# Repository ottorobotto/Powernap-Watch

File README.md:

# PowerNap PCB, spin 1

First circuit board for the PowerNap watch: 32 x 40 mm, 4 layers, 66 parts placed by the factory.
Design notes and the reasons behind every choice: `docs/pcb-spin1-design.md`. The case: `case/README.md`.

**Read section 5 ("What has and has not been checked") before paying for anything.**

## 1. What is in this folder

| Path | What |
|---|---|
| `PowerNap_spin1.kicad_pro` | Open this in KiCad 10 to look at the schematic and the board. |
| `fab/PowerNap_spin1_gerbers.zip` | The board itself, for JLCPCB ("Gerber file"). |
| `fab/PowerNap_spin1_bom.csv` | The parts list with JLCPCB part numbers ("BOM file"). |
| `fab/PowerNap_spin1_cpl.csv` | Where each part goes and how it is turned ("CPL file"). |
| `fab/PowerNap_spin1_board.step` | 3D model of the board. |
| `out/PowerNap_spin1_schematic.pdf` | The schematic as a PDF. |
| `out/board_report.txt`, `out/stock.txt` | The last automatic board check and the last stock check. |
| `out/final_top.png`, `final_bottom.png`, `final_in1_ground.png`, `final_in2_3v3.png` | Pictures of the four copper layers. |
| `scripts/` | The programs that generate all of the above from one description (`design.py`). |
| `case/` | The 3D-printed case. |

Nothing here was drawn by hand. `scripts/design.py` lists every part and what each pin connects to;
`scripts/placement.py` says where each part sits. To change the design, change those and rebuild (section 6).

## 2. What the board does differently from the Arduino prototype

- It uses the same processor (nRF52840, inside the u-blox BMD-340 module) on the **same pins** as the
  Arduino Nano 33 BLE. So it runs the same firmware and is programmed from the Arduino IDE as a "Nano 33 BLE".
- Pulse sensor (MAX30101) on the **underside**, alone, so it can touch the skin through the case.
- Accelerometer BMI270 (the one all naps were recorded with). No magnetometer, no temperature sensor.
- USB-C for charging, uploading and the serial log. LiPo charger (100 mA) on board.
- On/off slide switch. Charging works in both positions.
- Buzzer (4 kHz) instead of the breadboard beeper; user button on the side; reset button behind a pin-hole.
- Status lights like the Arduino's: red/green/blue, the yellow "L" light, plus a red charging light.
- Five holes (`J2`) for the programmer, three test points (1.8 V, LED supply, system voltage).

## 3. Ordering from JLCPCB

Prices change; treat the numbers as rough. The quote on the website is the real one.

1. Go to jlcpcb.com, choose **Instant Quote / Order now**, and upload `fab/PowerNap_spin1_gerbers.zip`.
   It should detect **4 layers, 32 x 40 mm**. If it does not, stop and ask.
2. Board options: quantity **5**; thickness **1.6 mm**; surface finish **ENIG** (flat gold pads — worth the extra
   for the fine-pitch module and sensors); via covering **tented**; everything else as offered.
3. Switch on **PCB Assembly**. Choose **Standard** assembly, **both sides** (the pulse sensor is on the underside),
   quantity 2 or 5. Let JLCPCB add tooling holes and edge rails. Tick **"Confirm parts placement"**.
4. Upload `PowerNap_spin1_bom.csv` and `PowerNap_spin1_cpl.csv`.
5. Parts page: every line should be found and in stock (checked on 15 November 2026, see `out/stock.txt`).
   `J2` and `BT1` are not in the files on purpose — nothing is soldered there by the factory.
   If a part is out of stock, do not accept a suggested replacement without asking.
6. **Placement preview — check these before you pay** (section 5 explains why):
   - `U6` (pulse sensor, underside): its pin-1 dot must match the dot printed on the board.
   - `U1` (the big module): antenna end at the board edge, at the top.
   - `J1` (USB-C): opening pointing out over the right-hand edge.
   - The small chips `U2 U3 U4 U5 U7 U8 Q1 Q2`: pin-1 dot on the board's pin-1 mark.
   - `LED1`–`LED5`, `D1`, `D2`, `LS1` (buzzer, `+` mark).
7. Rough cost for 5 boards, 2 of them assembled: boards about $25 with ENIG, assembly set-up about $50,
   18 "extended" part types x $3 = $54, parts about $24 per board, shipping about $25, then Danish VAT (25 %)
   and a handling fee on top. Expect **roughly 1,500–2,200 DKK** in total. Not a quote.

## 4. First start-up (when the boards arrive)

You need an **nRF52840 DK** (Nordic's development board, about 400 DKK) once, to put the Arduino bootloader
into each new board. A new module is blank and does not show up on USB until this is done.

1. Look before you power: no solder bridges, pulse sensor straight in its place.
2. With a multimeter, check there is **no short** between `3V3` (hole 1 of `J2`, the square one) and `GND` (hole 5).
3. Plug in USB **without a battery**, switch on. Measure: test point `TP3` about 4.6 V; `J2` hole 1 = 3.3 V
   (3.25–3.35). If the 3.3 V is missing or the board gets warm, unplug.
   (The red charge light may glow or flicker with no battery connected. That is normal.)
4. Bootloader: connect the DK's **Debug out** pins to `J2` — hole 1 = 3.3 V (the DK's "VTG"), 2 = SWDIO,
   3 = SWDCLK, 4 = RESET, 5 = GND — and program this file, which is already on your PC:
   `C:\Users\pc\AppData\Local\Arduino15\packages\arduino\hardware\mbed_nano\4.6.0\bootloaders\nano33ble\bootloader.hex`
   with Nordic's "Programmer" app (part of nRF Connect for Desktop). I will walk you through this step when
   you get there.
5. Press reset twice quickly: the yellow light should pulse and a new COM port should appear. From here on
   the board is programmed from the Arduino IDE exactly like the Nano.
6. Firmware: PowerNap v11 with **one line changed**: `IMU.begin()` becomes `IMU.begin(BOSCH_ACCELEROMETER_ONLY)`
   (there is no magnetometer on this board, and the library otherwise waits for one).
   The new buzzer is a different type from the breadboard one, so the quiet "probe" beep (`PROBE_DUTY`)
   needs re-tuning by ear.
7. Only then solder the battery to `BT1` — **measure which wire is + first**. With the battery in, the red
   light is on while charging and goes out when full.

## 5. What has and has not been checked

Checked by program, every time the board is rebuilt:

- The schematic passes KiCad's electrical rule check with 0 messages, and its netlist is identical to `design.py`
  (every net, every pin).
- The board passes KiCad's design rule check with 0 errors (clearances, track widths, shorts, unconnected
  pins, parts overlapping) and matches the schematic part for part and pin for pin. See `out/board_report.txt`.
  What remains are 5 cosmetic notes about silkscreen lines running over the board edge at the USB socket
  and the switches; the factory simply cuts those off.
- No copper in the strip under the antenna. The ground-plane layer carries no tracks at all - it is one
  unbroken sheet (`out/final_in1_ground.png`).
- Every footprint was compared pad by pad with the footprint JLCPCB uses for the same part number, and the
  rotations in the placement file were calculated from that comparison (`scripts/check_rotations.py`).
- The finished placement file was then tested the way the factory uses it: JLCPCB's footprint for each of
  the 66 parts was placed at the file's position and rotation, and its pads compared with the board's.
  All land on their pads; the largest difference is 0.28 mm (`scripts/verify_cpl.py`).
- All 36 part types were in stock at JLCPCB on 15 November 2026.

Checked by me against documents:

- Every pin of every chip against its data sheet or a proven schematic (sources are listed at the top of `design.py`).
- The module's 68-pad footprint against the data sheet drawing and against JLCPCB's own footprint.

**Not checked — the real risks:**

1. **Nobody experienced has looked at this layout.** It was placed by coordinates and routed by programs
   (an automatic router, plus a small one I wrote for the last 22 connections). It obeys the rules, but rules
   do not catch everything (noise near the sensor, radio range, how well it solders). Known blemishes:
   about 37 mm of the 3.3 V and USB supply runs in 0.15 mm tracks instead of the usual 0.25 mm (still several
   times more than the current needs), and one small via sits right against a resistor pad (`R16`). For a first board that is normal, and it is why this is "spin 1" — but if you know
   anyone who designs boards, an hour of their time before ordering is the best money-saver there is.
2. **The underside part's rotation** (`U6`, the pulse sensor) follows the usual convention for bottom-side
   parts (mirrored, angle counted from below), which I could not confirm in JLCPCB's own documentation.
   If it were wrong the sensor would be soldered on turned by half a turn and would not work. That is why
   step 6 of the ordering list matters; JLCPCB's engineers also check pin-1 marks.
3. **The Arduino bootloader on this module** should work (same chip, same pins), but it has not been tried.
4. **The buzzer's loudness** inside the case, and the **radio range** with the battery beside the module,
   are unknown until a board exists.
5. Nothing has been built. A first board commonly needs one or two wire fixes; a second spin is the usual outcome.

## 6. Rebuilding after a change

Run from the project folder, in this order. `KP` means `"C:\Program Files\KiCad\10.0\bin\python.exe"`.

1. `py -3.11 hardware/spin1/scripts/gen_schematic.py` — writes the schematic
2. `py -3.11 hardware/spin1/scripts/verify_schematic.py` — must end with `SCHEMATIC OK`
3. `KP hardware/spin1/scripts/gen_board.py` — places the parts
4. `KP hardware/spin1/scripts/route_board.py` — routes (about 10 minutes). The automatic router does not give
   the same result twice; add `--reuse` to keep its last result and only redo the steps after it.
5. `KP hardware/spin1/scripts/verify_board.py` — must end with `BOARD OK`
6. `KP hardware/spin1/scripts/check_rotations.py` — only if a part or footprint changed
7. `py -3.11 hardware/spin1/scripts/export_fab.py` — writes `fab/`
8. `KP hardware/spin1/scripts/verify_cpl.py` — must end with `PLACEMENT FILE OK`
9. `py -3.11 hardware/spin1/scripts/check_stock.py` — live stock
10. `KP hardware/spin1/scripts/dump_bodies.py`, then Blender with `case/build_case.py` — rebuilds the case

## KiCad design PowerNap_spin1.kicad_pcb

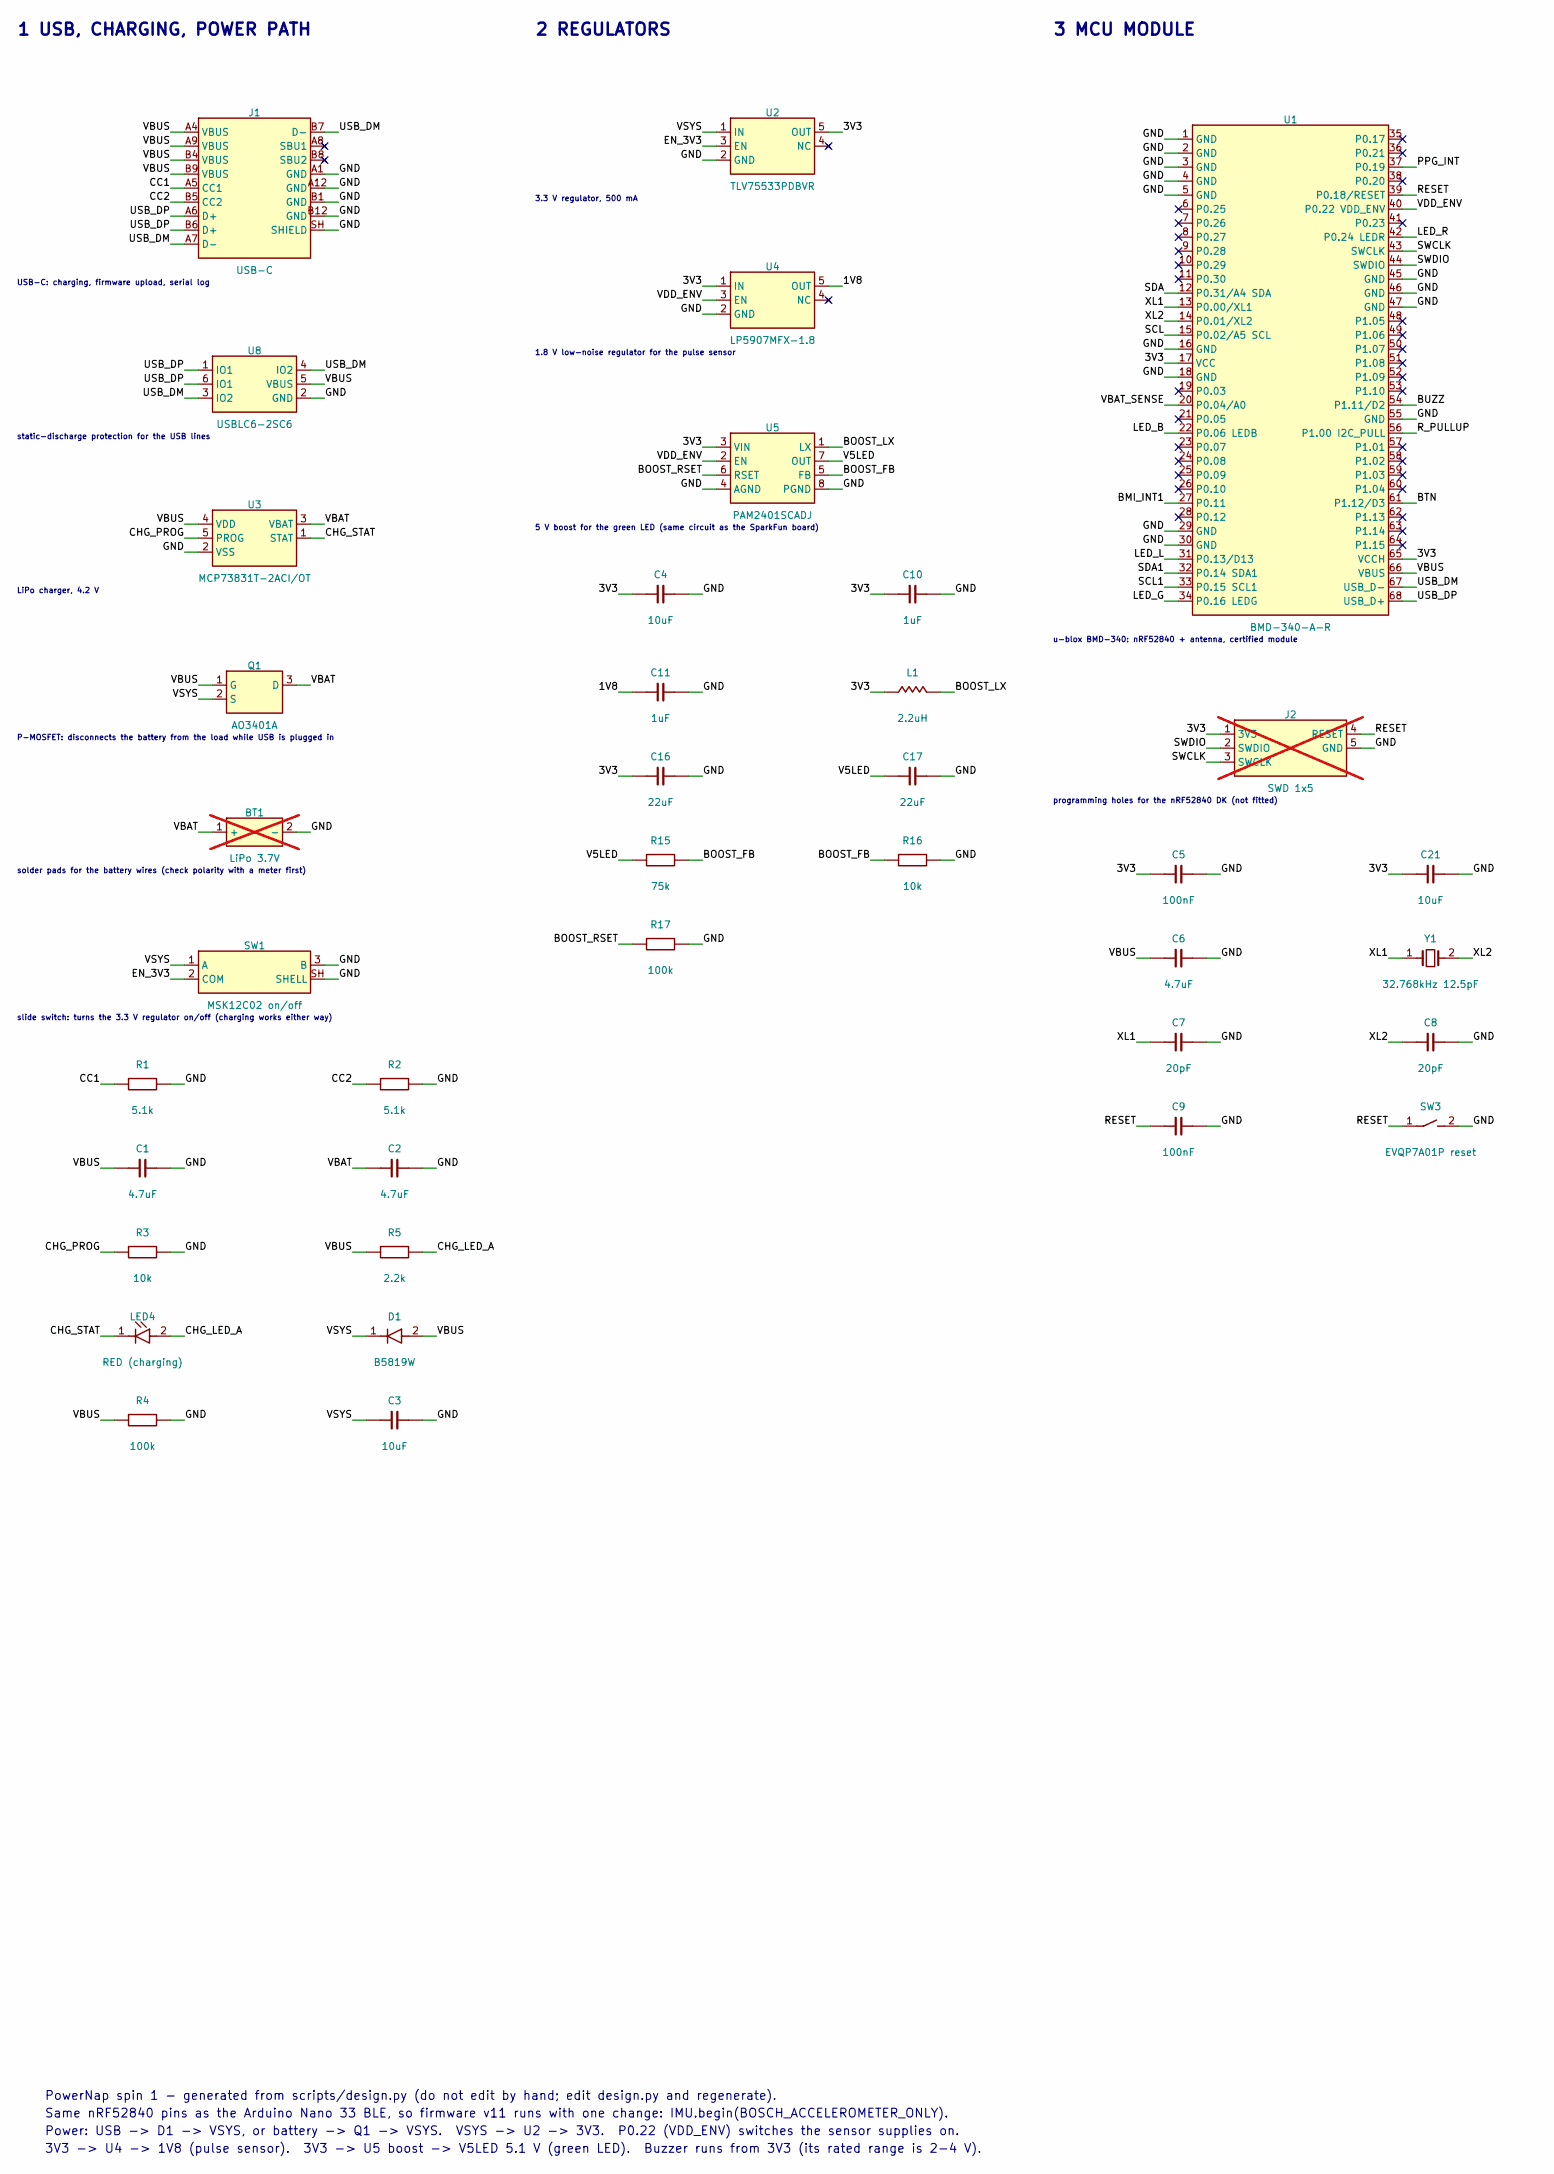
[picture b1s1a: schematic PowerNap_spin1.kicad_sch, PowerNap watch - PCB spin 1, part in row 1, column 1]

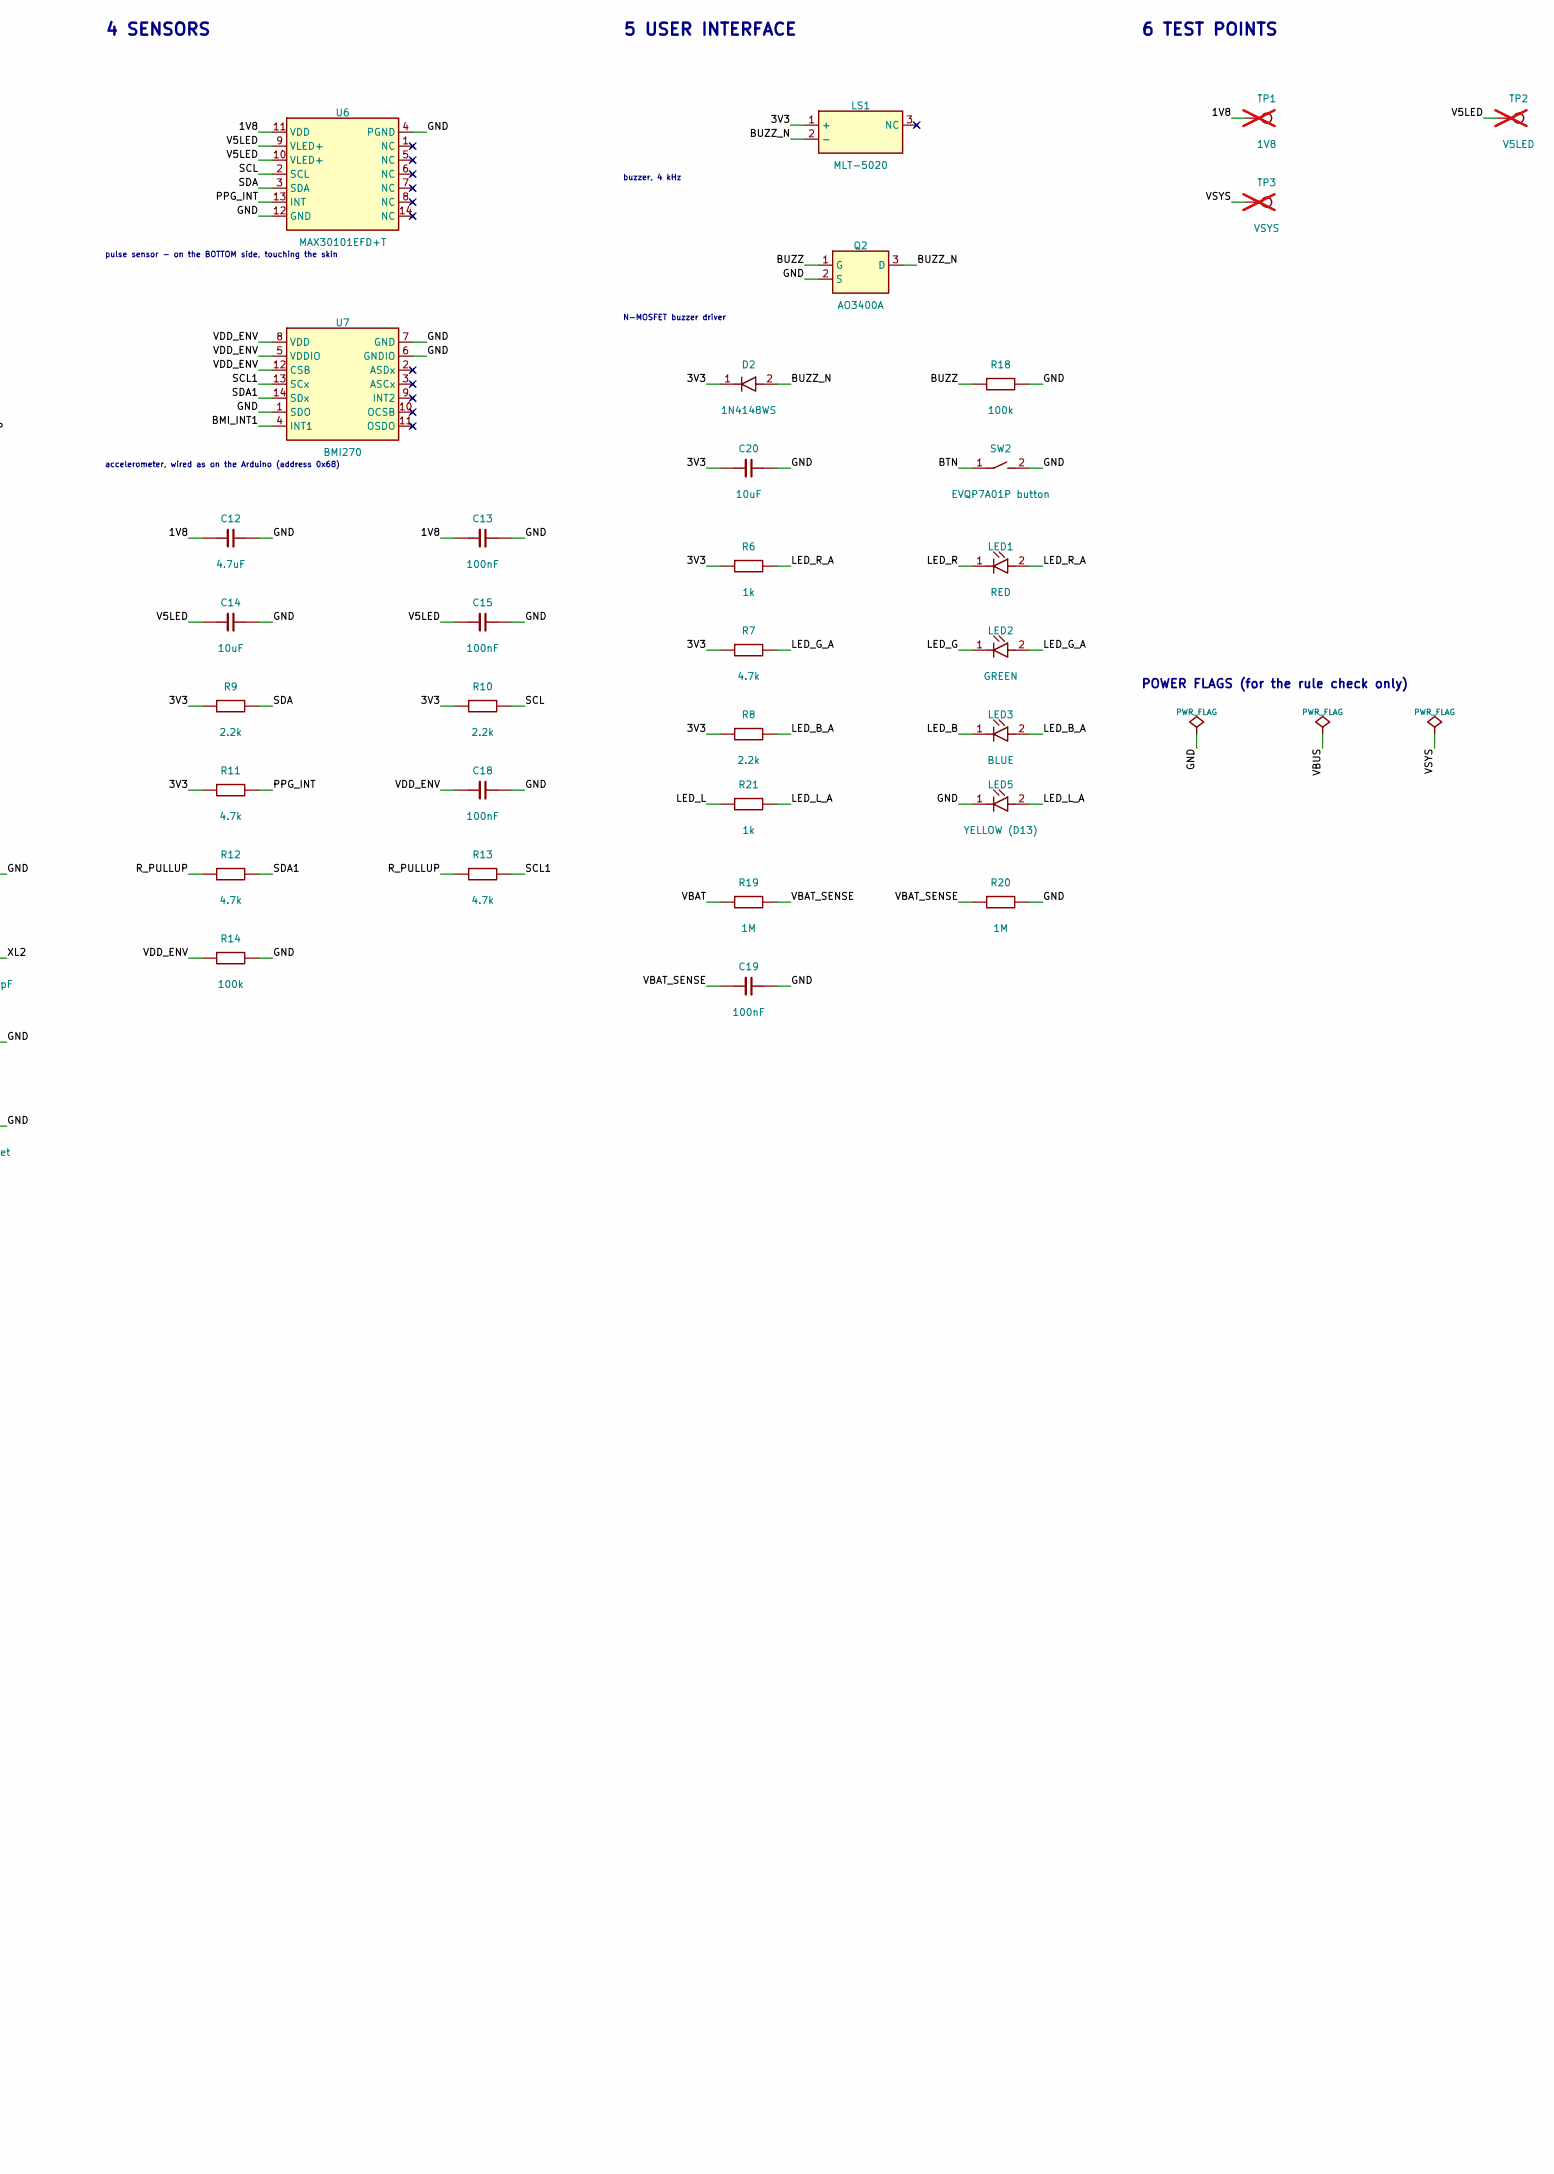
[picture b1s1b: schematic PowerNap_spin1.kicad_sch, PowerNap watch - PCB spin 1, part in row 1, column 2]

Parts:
BT1: LiPo 3.7V; BatteryPads; MPN LiPo 3.7V; not fitted
C1, C2, C6, C12: 4.7uF; C_0402_1005Metric; MPN SMD:C 4.7uF; LCSC C23733
C3, C4, C14, C20, C21: 10uF; C_0603_1608Metric; MPN SMD:C 10uF; LCSC C19702
C5, C9, C13, C15, C18, C19: 100nF; C_0402_1005Metric; MPN SMD:C 100nF; LCSC C1525
C7, C8: 20pF; C_0402_1005Metric; MPN SMD:C 20pF; LCSC C1554
C10, C11: 1uF; C_0402_1005Metric; MPN SMD:C 1uF; LCSC C52923
C16, C17: 22uF; C_0603_1608Metric; MPN SMD:C 22uF; LCSC C59461
D1: B5819W; D_SOD-123; MPN B5819W; LCSC C8598
D2: 1N4148WS; D_SOD-323; MPN 1N4148WS; LCSC C2128
J1: USB-C; USB_C_Receptacle_HRO_TYPE-C-31-M-12; MPN HRO TYPE-C-31-M-12; LCSC C165948
J2: SWD 1x5; PinHeader_1x05_P2.54mm_Vertical; MPN SWD 1x5; not fitted
L1: 2.2uH; L_Sunlord_SWPA3015S; MPN SWPA3015S2R2MT; LCSC C43389
LED1: RED; LED_0603_1608Metric; MPN KT-0603R; LCSC C2286
LED2: GREEN; LED_0603_1608Metric; MPN XL-1608UGC-04; LCSC C965804
LED3: BLUE; LED_0603_1608Metric; MPN XL-1608UBC-04; LCSC C965807
LED4: RED (charging); LED_0603_1608Metric; MPN KT-0603R; LCSC C2286
LED5: YELLOW (D13); LED_0603_1608Metric; MPN XL-1608UYC-06; LCSC C965802
LS1: MLT-5020; MPN MLT-5020; LCSC C94598
Q1: AO3401A; SOT-23; MPN AO3401A; LCSC C15127
Q2: AO3400A; SOT-23; MPN AO3400A; LCSC C20917
R1, R2: 5.1k; R_0402_1005Metric; MPN 0402 5.1k 1%; LCSC C25905
R3, R16: 10k; R_0402_1005Metric; MPN 0402 10k 1%; LCSC C25744
R4, R14, R17, R18: 100k; R_0402_1005Metric; MPN 0402 100k 1%; LCSC C25741
R5, R8, R9, R10: 2.2k; R_0402_1005Metric; MPN 0402 2.2k 1%; LCSC C25879
R6, R21: 1k; R_0402_1005Metric; MPN 0402 1k 1%; LCSC C11702
R7, R11, R12, R13: 4.7k; R_0402_1005Metric; MPN 0402 4.7k 1%; LCSC C25900
R15: 75k; R_0402_1005Metric; MPN 0402 75k 1%; LCSC C25798
R19, R20: 1M; R_0402_1005Metric; MPN 0402 1M 1%; LCSC C26083
SW1: MSK12C02 on/off; SW_SPDT_Shouhan_MSK12C02; MPN MSK12C02; LCSC C431540
SW2: EVQP7A01P button; SW_SPST_EVQP7A; MPN EVQP7A01P; LCSC C79167
SW3: EVQP7A01P reset; SW_SPST_EVQP7A; MPN EVQP7A01P; LCSC C79167
TP1: 1V8; TestPoint_Pad_D1.0mm; MPN 1V8; not fitted
TP2: V5LED; TestPoint_Pad_D1.0mm; MPN V5LED; not fitted
TP3: VSYS; TestPoint_Pad_D1.0mm; MPN VSYS; not fitted
U1: BMD-340-A-R; BMD-340; MPN BMD-340-A-R; LCSC C5456944
U2: TLV75533PDBVR; SOT-23-5; MPN TLV75533PDBVR; LCSC C404027
U3: MCP73831T-2ACI/OT; SOT-23-5; MPN MCP73831T-2ACI/OT; LCSC C424093
U4: LP5907MFX-1.8; SOT-23-5; MPN LP5907MFX-1.8/NOPB; LCSC C92498
U5: PAM2401SCADJ; MSOP-8_3x3mm_P0.65mm; MPN PAM2401SCADJ; LCSC C508238
U6: MAX30101EFD+T; Maxim_OLGA-14_3.3x5.6mm_P0.8mm; MPN MAX30101EFD+T; LCSC C2859066
U7: BMI270; Bosch_LGA-14_3x2.5mm_P0.5mm; MPN BMI270; LCSC C2836813
U8: USBLC6-2SC6; SOT-23-6; MPN USBLC6-2SC6; LCSC C7519
Y1: 32.768kHz 12.5pF; Crystal_SMD_3215-2Pin_3.2x1.5mm; MPN X321532768KGD2SI; LCSC C620155

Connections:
/1V8: C11.1, C12.1, C13.1, TP1.1, U4.5 (OUT), U6.11 (VDD)
/3V3: C4.1, C5.1, C10.1, C16.1, C20.1, C21.1, D2.1, J2.1 (3V3), L1.1, LS1.1 (+), R6.1, R7.1, R8.1, R9.1, R10.1, R11.1, U1.17 (VCC), U1.65 (VCCH), U2.5 (OUT), U4.1 (IN), U5.3 (VIN)
/BMI_INT1: U1.27 (P0.11), U7.4 (INT1)
/BOOST_FB: R15.2, R16.1, U5.5 (FB)
/BOOST_LX: L1.2, U5.1 (LX)
/BOOST_RSET: R17.1, U5.6 (RSET)
/BTN: SW2.1, U1.61 (P1.12/D3)
/BUZZ: Q2.1 (G), R18.1, U1.54 (P1.11/D2)
/BUZZ_N: D2.2, LS1.2 (-), Q2.3 (D)
/CC1: J1.A5 (CC1), R1.1
/CC2: J1.B5 (CC2), R2.1
/CHG_LED_A: LED4.2, R5.2
/CHG_PROG: R3.1, U3.5 (PROG)
/CHG_STAT: LED4.1, U3.1 (STAT)
/EN_3V3: SW1.2 (COM), U2.3 (EN)
/GND: BT1.2 (-), C1.2, C2.2, C3.2, C4.2, C5.2, C6.2, C7.2, C8.2, C9.2, C10.2, C11.2, C12.2, C13.2, C14.2, C15.2, C16.2, C17.2, C18.2, C19.2, C20.2, C21.2, J1.A1 (GND), J1.A12 (GND), J1.B1 (GND), J1.B12 (GND), J1.SH (SHIELD), J2.5 (GND), LED5.1, Q2.2 (S), R1.2, R2.2, R3.2, R4.2, R14.2, R16.2, R17.2, R18.2, R20.2, SW1.3 (B), SW1.SH (SHELL), SW2.2, SW3.2, U1.1 (GND), U1.2 (GND), U1.3 (GND), U1.4 (GND), U1.5 (GND), U1.16 (GND), U1.18 (GND), U1.29 (GND), U1.30 (GND), U1.45 (GND), U1.46 (GND), U1.47 (GND), U1.55 (GND), U2.2 (GND), U3.2 (VSS), U4.2 (GND), U5.4 (AGND), U5.8 (PGND), U6.4 (PGND), U6.12 (GND), U7.1 (SDO), U7.6 (GNDIO), U7.7 (GND), U8.2 (GND)
/LED_B: LED3.1, U1.22 (P0.06 LEDB)
/LED_B_A: LED3.2, R8.2
/LED_G: LED2.1, U1.34 (P0.16 LEDG)
/LED_G_A: LED2.2, R7.2
/LED_L: R21.1, U1.31 (P0.13/D13)
/LED_L_A: LED5.2, R21.2
/LED_R: LED1.1, U1.42 (P0.24 LEDR)
/LED_R_A: LED1.2, R6.2
/PPG_INT: R11.2, U1.37 (P0.19), U6.13 (INT)
/RESET: C9.1, J2.4 (RESET), SW3.1, U1.39 (P0.18/RESET)
/R_PULLUP: R12.1, R13.1, U1.56 (P1.00 I2C_PULL)
/SCL: R10.2, U1.15 (P0.02/A5 SCL), U6.2 (SCL)
/SCL1: R13.2, U1.33 (P0.15 SCL1), U7.13 (SCx)
/SDA: R9.2, U1.12 (P0.31/A4 SDA), U6.3 (SDA)
/SDA1: R12.2, U1.32 (P0.14 SDA1), U7.14 (SDx)
/SWCLK: J2.3 (SWCLK), U1.43 (SWCLK)
/SWDIO: J2.2 (SWDIO), U1.44 (SWDIO)
/USB_DM: J1.A7 (D-), J1.B7 (D-), U1.67 (USB_D-), U8.3 (IO2), U8.4 (IO2)
/USB_DP: J1.A6 (D+), J1.B6 (D+), U1.68 (USB_D+), U8.1 (IO1), U8.6 (IO1)
/V5LED: C14.1, C15.1, C17.1, R15.1, TP2.1, U5.7 (OUT), U6.9 (VLED+), U6.10 (VLED+)
/VBAT: BT1.1 (+), C2.1, Q1.3 (D), R19.1, U3.3 (VBAT)
/VBAT_SENSE: C19.1, R19.2, R20.1, U1.20 (P0.04/A0)
/VBUS: C1.1, C6.1, D1.2, J1.A4 (VBUS), J1.A9 (VBUS), J1.B4 (VBUS), J1.B9 (VBUS), Q1.1 (G), R4.1, R5.1, U1.66 (VBUS), U3.4 (VDD), U8.5 (VBUS)
/VDD_ENV: C18.1, R14.1, U1.40 (P0.22 VDD_ENV), U4.3 (EN), U5.2 (EN), U7.5 (VDDIO), U7.8 (VDD), U7.12 (CSB)
/VSYS: C3.1, D1.1, Q1.2 (S), SW1.1 (A), TP3.1, U2.1 (IN)
/XL1: C7.1, U1.13 (P0.00/XL1), Y1.1
/XL2: C8.1, U1.14 (P0.01/XL2), Y1.2

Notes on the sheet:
1 USB, CHARGING, POWER PATH
USB-C: charging, firmware upload, serial log
static-discharge protection for the USB lines
LiPo charger, 4.2 V
P-MOSFET: disconnects the battery from the load while USB is plugged in
solder pads for the battery wires (check polarity with a meter first)
slide switch: turns the 3.3 V regulator on/off (charging works either way)
2 REGULATORS
3.3 V regulator, 500 mA
1.8 V low-noise regulator for the pulse sensor
5 V boost for the green LED (same circuit as the SparkFun board)
3 MCU MODULE
u-blox BMD-340: nRF52840 + antenna, certified module
programming holes for the nRF52840 DK (not fitted)
4 SENSORS
pulse sensor - on the BOTTOM side, touching the skin
accelerometer, wired as on the Arduino (address 0x68)
5 USER INTERFACE
buzzer, 4 kHz
N-MOSFET buzzer driver
6 TEST POINTS
POWER FLAGS (for the rule check only)
PowerNap spin 1 - generated from scripts/design.py (do not edit by hand; edit design.py and regenerate).
Same nRF52840 pins as the Arduino Nano 33 BLE, so firmware v11 runs with one change: IMU.begin(BOSCH_ACCELEROMETER_ONLY).
Power: USB -> D1 -> VSYS, or battery -> Q1 -> VSYS. VSYS -> U2 -> 3V3. P0.22 (VDD_ENV) switches the sensor supplies on.
3V3 -> U4 -> 1V8 (pulse sensor). 3V3 -> U5 boost -> V5LED 5.1 V (green LED). Buzzer runs from 3V3 (its rated range is 2-4 V).

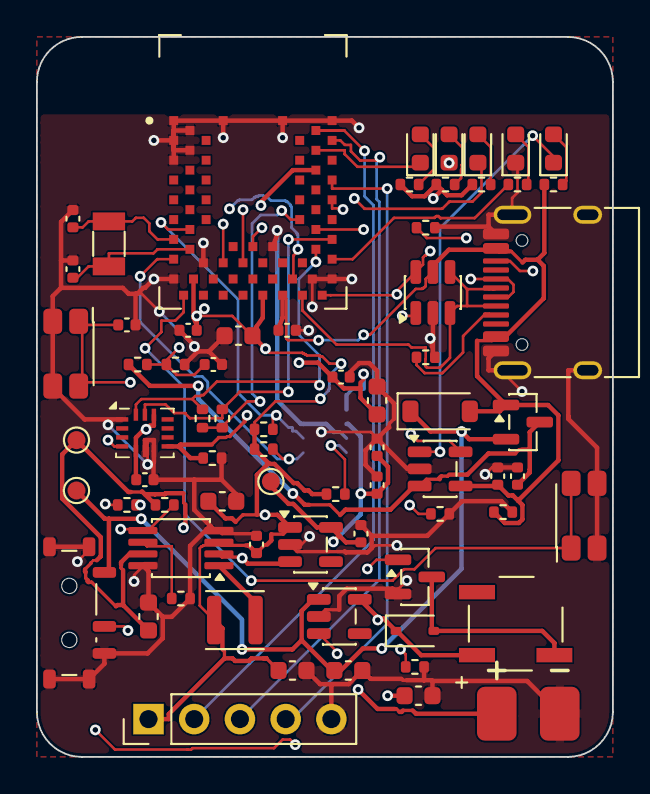
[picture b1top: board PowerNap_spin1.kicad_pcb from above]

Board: 4 copper layers, 32.0 x 40.0 mm, 71 parts (1 on the bottom side), 43 nets.

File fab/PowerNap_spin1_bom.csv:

Comment,Designator,Footprint,LCSC Part #
4.7uF,"C1,C2,C6,C12",C_0402_1005Metric,C23733
1uF,"C10,C11",C_0402_1005Metric,C52923
22uF,"C16,C17",C_0603_1608Metric,C59461
10uF,"C3,C4,C21,C14,C20",C_0603_1608Metric,C19702
100nF,"C5,C9,C13,C15,C18,C19",C_0402_1005Metric,C1525
20pF,"C7,C8",C_0402_1005Metric,C1554
B5819W,D1,D_SOD-123,C8598
1N4148WS,D2,D_SOD-323,C2128
HRO TYPE-C-31-M-12,J1,USB_C_Receptacle_HRO_TYPE-C-31-M-12,C165948
SWPA3015S2R2MT,L1,L_Sunlord_SWPA3015S,C43389
XL-1608UGC-04,LED2,LED_0603_1608Metric,C965804
XL-1608UBC-04,LED3,LED_0603_1608Metric,C965807
KT-0603R,"LED4,LED1",LED_0603_1608Metric,C2286
XL-1608UYC-06,LED5,LED_0603_1608Metric,C965802
MLT-5020,LS1,MLT-5020,C94598
AO3401A,Q1,SOT-23,C15127
AO3400A,Q2,SOT-23,C20917
5.1k,"R1,R2",R_0402_1005Metric,C25905
4.7k,"R11,R12,R13,R7",R_0402_1005Metric,C25900
75k,R15,R_0402_1005Metric,C25798
1M,"R19,R20",R_0402_1005Metric,C26083
10k,"R3,R16",R_0402_1005Metric,C25744
100k,"R4,R17,R14,R18",R_0402_1005Metric,C25741
2.2k,"R5,R9,R10,R8",R_0402_1005Metric,C25879
1k,"R6,R21",R_0402_1005Metric,C11702
MSK12C02,SW1,SW_SPDT_Shouhan_MSK12C02,C431540
EVQP7A01P,"SW3,SW2",SW_SPST_EVQP7A,C79167
BMD-340-A-R,U1,BMD-340,C5456944
TLV75533PDBVR,U2,SOT-23-5,C404027
MCP73831T-2ACI/OT,U3,SOT-23-5,C424093
LP5907MFX-1.8/NOPB,U4,SOT-23-5,C92498
PAM2401SCADJ,U5,MSOP-8_3x3mm_P0.65mm,C508238
MAX30101EFD+T,U6,Maxim_OLGA-14_3.3x5.6mm_P0.8mm,C2859066
BMI270,U7,Bosch_LGA-14_3x2.5mm_P0.5mm,C2836813
USBLC6-2SC6,U8,SOT-23-6,C7519
X321532768KGD2SI,Y1,Crystal_SMD_3215-2Pin_3.2x1.5mm,C620155
